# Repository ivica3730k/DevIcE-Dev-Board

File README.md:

# DevIcE-Development-Board
All software materials for DevIcE Development board,created by Ivica 9A3ICE

IoT development board currently is based on ESP8266,including:
SMPS power supply
16 digital IO ports
6 ADC ports
5 DAC outputs
RTC clock
Optional HC-05 bluetooth

...all packed in small form factor of 100*60mm.

Board easly programmable trough Arduino IDE

Full board plans available in other Repo.

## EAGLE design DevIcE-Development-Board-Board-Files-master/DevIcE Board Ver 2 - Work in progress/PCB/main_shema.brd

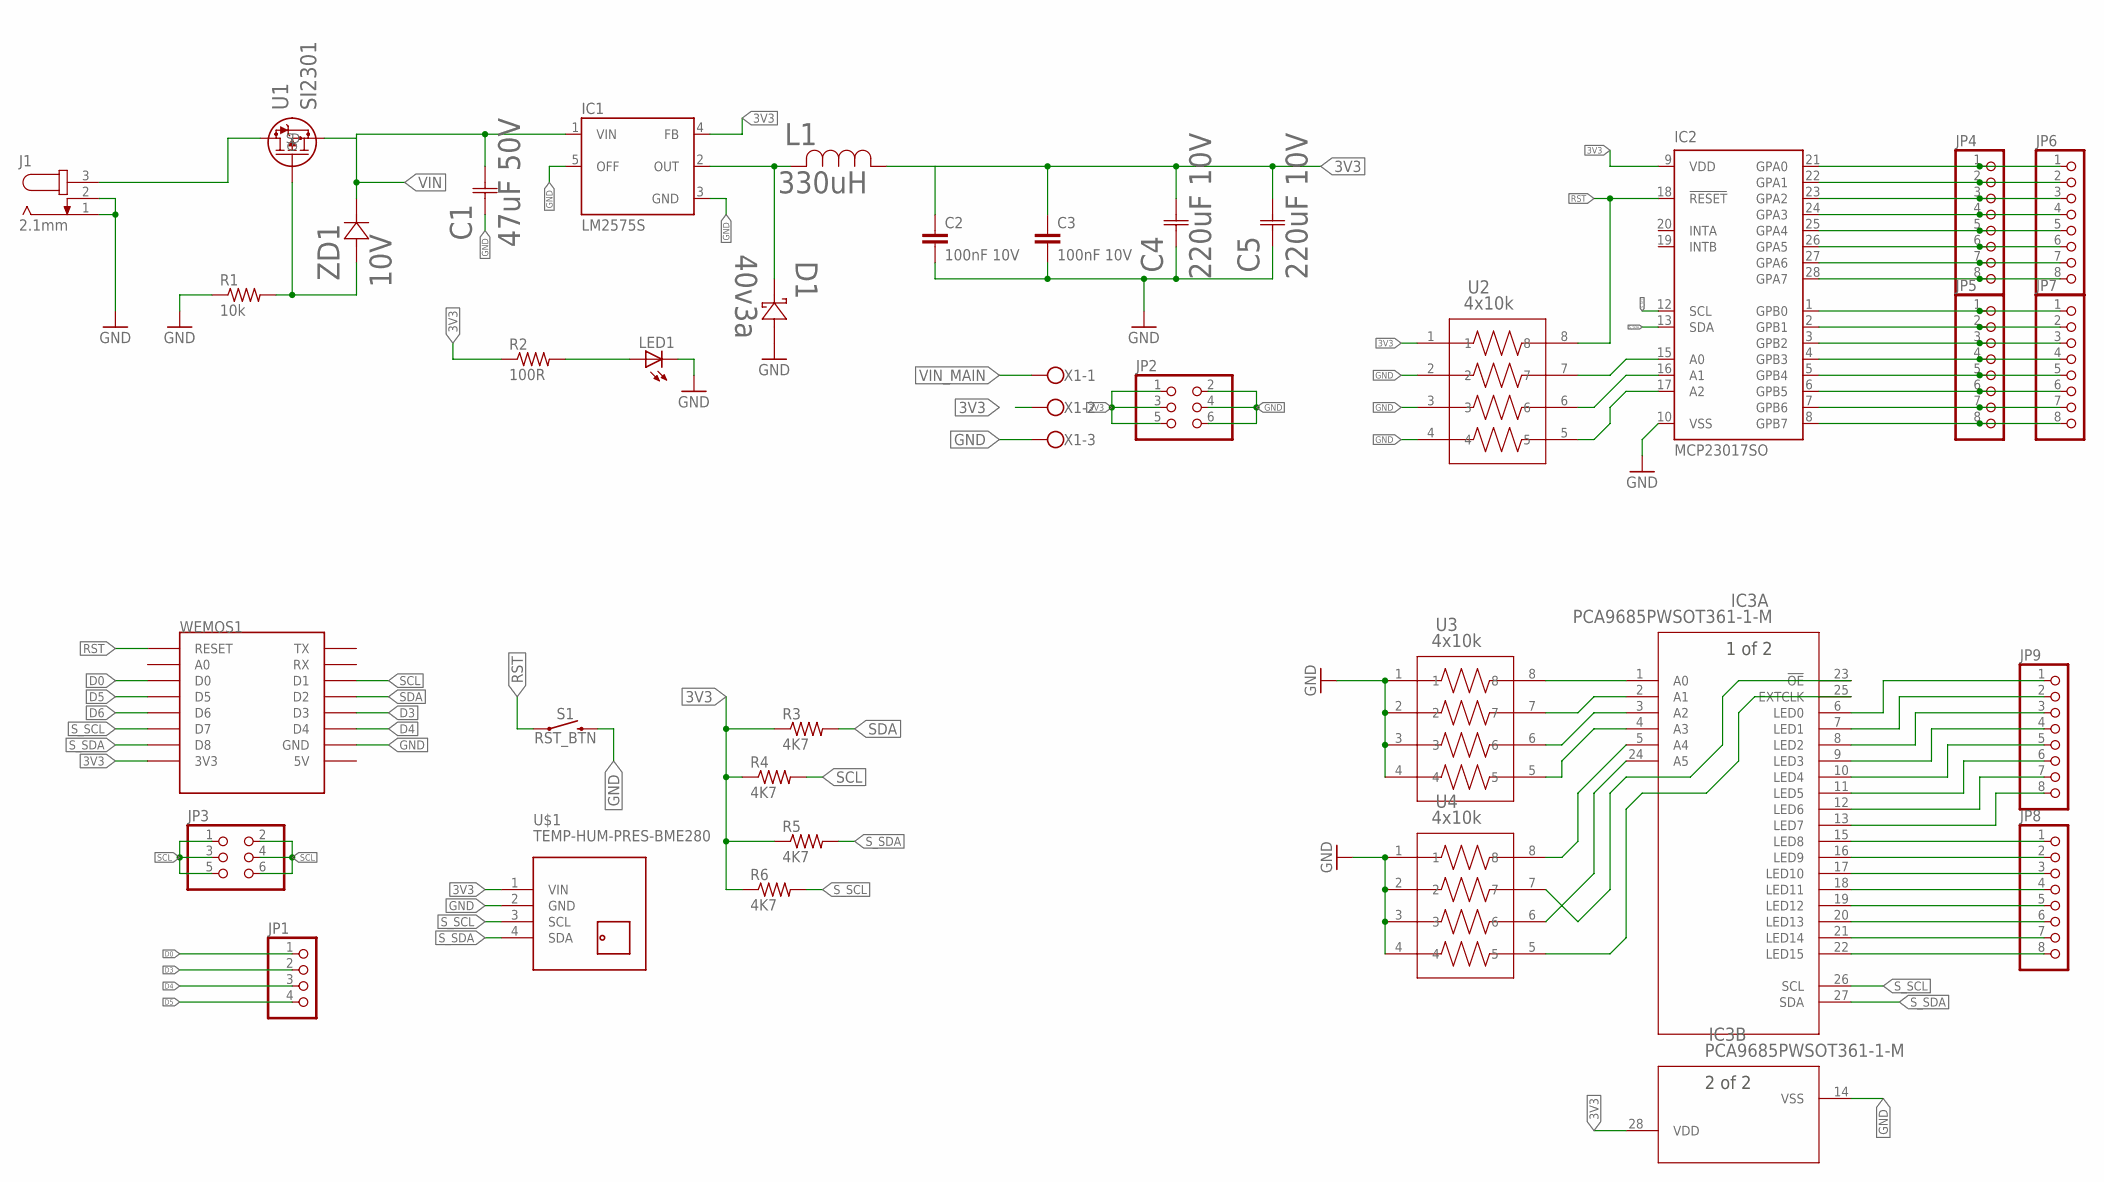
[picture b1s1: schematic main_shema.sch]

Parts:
C1: 47uF 50V; CAP_EEE_D8-M
C2, C3: 100nF 10V; C0603
C4, C5: 220uF 10V; CAP_EEE_D-M
D1: 40v3a; CDBA-HF-M
IC1: LM2575S; TO263-5
IC2: MCP23017SO; SO28W
IC3: PCA9685PWSOT361-1-M; SOT361-1-M
J1: 2.1mm; SPC4078
JP1: PINHD-1X4; 1X04
JP2, JP3: PINHD-2X3; 2X03
JP4, JP5, JP6, JP7: PINHD-1X8; 1X08
JP8, JP9: PINHD-1X8/LONG; 1X08
L1: 330uH; IND_BOURNS_SRR1280
LED1: LED_E; LED_1206
R1: 10k; R0603
R2: 100R; R0603
R3, R4, R5, R6: 4K7; R0603
S1: RST_BTN; TACTILE_SWITCH_PTH_6.0MM
U1: SI2301; TO-236-M
U2: 4x10k; C_ARRAY_EXB38V
U3, U4: 4x10k; C_ARRAY_EXB38V-M
U$1: TEMP-HUM-PRES-BME280
WEMOS1: WEMOS-D1-MINI
X1: W237-103
ZD1: 10V; SMINI2-F5-B-M

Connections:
3V3: C2.1, C3.1, C4.2 (22), C5.2 (22), IC1.4 (FB), IC2.9 (VDD), IC3.28 (VDD), JP2.1, JP2.3, JP2.5, L1.1, R2.1, R3.1, R4.1, R5.1, R6.1, U2.1, U$1.1 (VIN), WEMOS1.3V3, X1.2
D0: JP1.1, WEMOS1.D0
D3: JP1.2, WEMOS1.D3
D4: JP1.3, WEMOS1.D4
D5: JP1.4, WEMOS1.D5
D6: WEMOS1.D6
GND: C1.1 (11), C2.2, C3.2, C4.1 (11), C5.1 (11), D1.2 (22), IC1.3 (GND), IC1.5 (OFF), IC2.10 (VSS), IC3.14 (VSS), J1.1, J1.2, JP2.2, JP2.4, JP2.6, LED1.C, R1.1, S1.3 (2), U2.2, U2.3, U2.4, U3.1, U3.2, U3.3, U3.4, U4.1, U4.2, U4.3, U4.4, U$1.2 (GND), WEMOS1.GND, X1.3
unnamed: LED1.A, R2.2
unnamed: R1.2, U1.1 (G), ZD1.2 (22)
unnamed: IC2.21 (GPA0), JP4.1, JP6.1
unnamed: IC2.22 (GPA1), JP4.2, JP6.2
unnamed: IC3.6 (LED0), JP9.1
unnamed: IC3.7 (LED1), JP9.2
unnamed: IC3.8 (LED2), JP9.3
unnamed: D1.1 (11), IC1.2 (OUT), L1.2
unnamed: IC2.15 (A0), U2.7
unnamed: IC3.9 (LED3), JP9.4
unnamed: IC2.23 (GPA2), JP4.3, JP6.3
unnamed: IC2.16 (A1), U2.6
unnamed: IC2.17 (A2), U2.5
unnamed: IC3.10 (LED4), JP9.5
unnamed: IC2.24 (GPA3), JP4.4, JP6.4
unnamed: IC2.25 (GPA4), JP4.5, JP6.5
unnamed: IC2.26 (GPA5), JP4.6, JP6.6
unnamed: IC3.11 (LED5), JP9.6
unnamed: IC3.12 (LED6), JP9.7
unnamed: IC3.13 (LED7), JP9.8
unnamed: IC2.27 (GPA6), JP4.7, JP6.7
unnamed: IC2.28 (GPA7), JP4.8, JP6.8
unnamed: IC2.1 (GPB0), JP5.1, JP7.1
unnamed: IC2.2 (GPB1), JP5.2, JP7.2
unnamed: IC2.3 (GPB2), JP5.3, JP7.3
unnamed: IC2.4 (GPB3), JP5.4, JP7.4
unnamed: IC2.5 (GPB4), JP5.5, JP7.5
unnamed: IC2.6 (GPB5), JP5.6, JP7.6
unnamed: IC2.7 (GPB6), JP5.7, JP7.7
unnamed: IC2.8 (GPB7), JP5.8, JP7.8
unnamed: IC3.15 (LED8), JP8.1
unnamed: IC3.16 (LED9), JP8.2
unnamed: IC3.17 (LED10), JP8.3
unnamed: IC3.18 (LED11), JP8.4
unnamed: IC3.19 (LED12), JP8.5
unnamed: IC3.20 (LED13), JP8.6
unnamed: IC3.21 (LED14), JP8.7
unnamed: IC3.22 (LED15), JP8.8
unnamed: IC3.1 (A0), U3.8
unnamed: IC3.2 (A1), U3.7
unnamed: IC3.3 (A2), U3.6
unnamed: IC3.4 (A3), U3.5
unnamed: IC3.5 (A4), U4.8
unnamed: IC3.24 (A5), U4.6
unnamed: IC3.23 (!OE), U4.7
unnamed: IC3.25 (EXTCLK), U4.5
RST: IC2.18 (!RESET), S1.1, U2.8, WEMOS1.RESET
SCL: JP3.1, JP3.3, JP3.5, R4.2, WEMOS1.D1
SDA: JP3.2, JP3.4, JP3.6, R3.2, WEMOS1.D2
S_SCL: IC2.12 (SCL), IC3.26 (SCL), R6.2, U$1.3 (SCL), WEMOS1.D7
S_SDA: IC2.13 (SDA), IC3.27 (SDA), R5.2, U$1.4 (SDA), WEMOS1.D8
VIN: C1.2 (22), IC1.1 (VIN), U1.2 (S), ZD1.1 (11)
VIN_MAIN: J1.3, U1.3 (D), X1.1

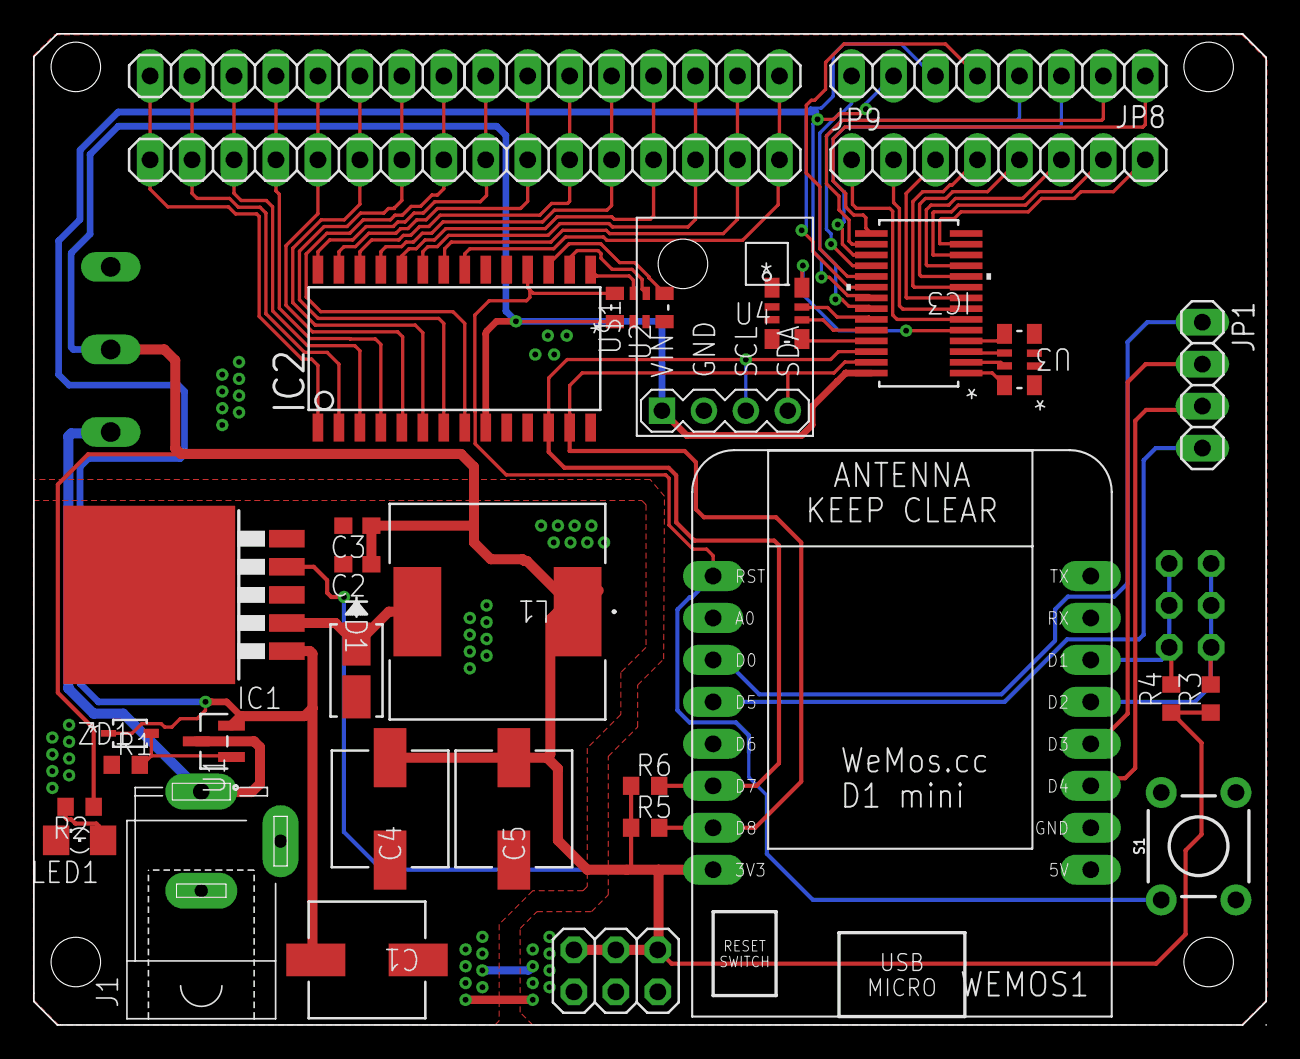
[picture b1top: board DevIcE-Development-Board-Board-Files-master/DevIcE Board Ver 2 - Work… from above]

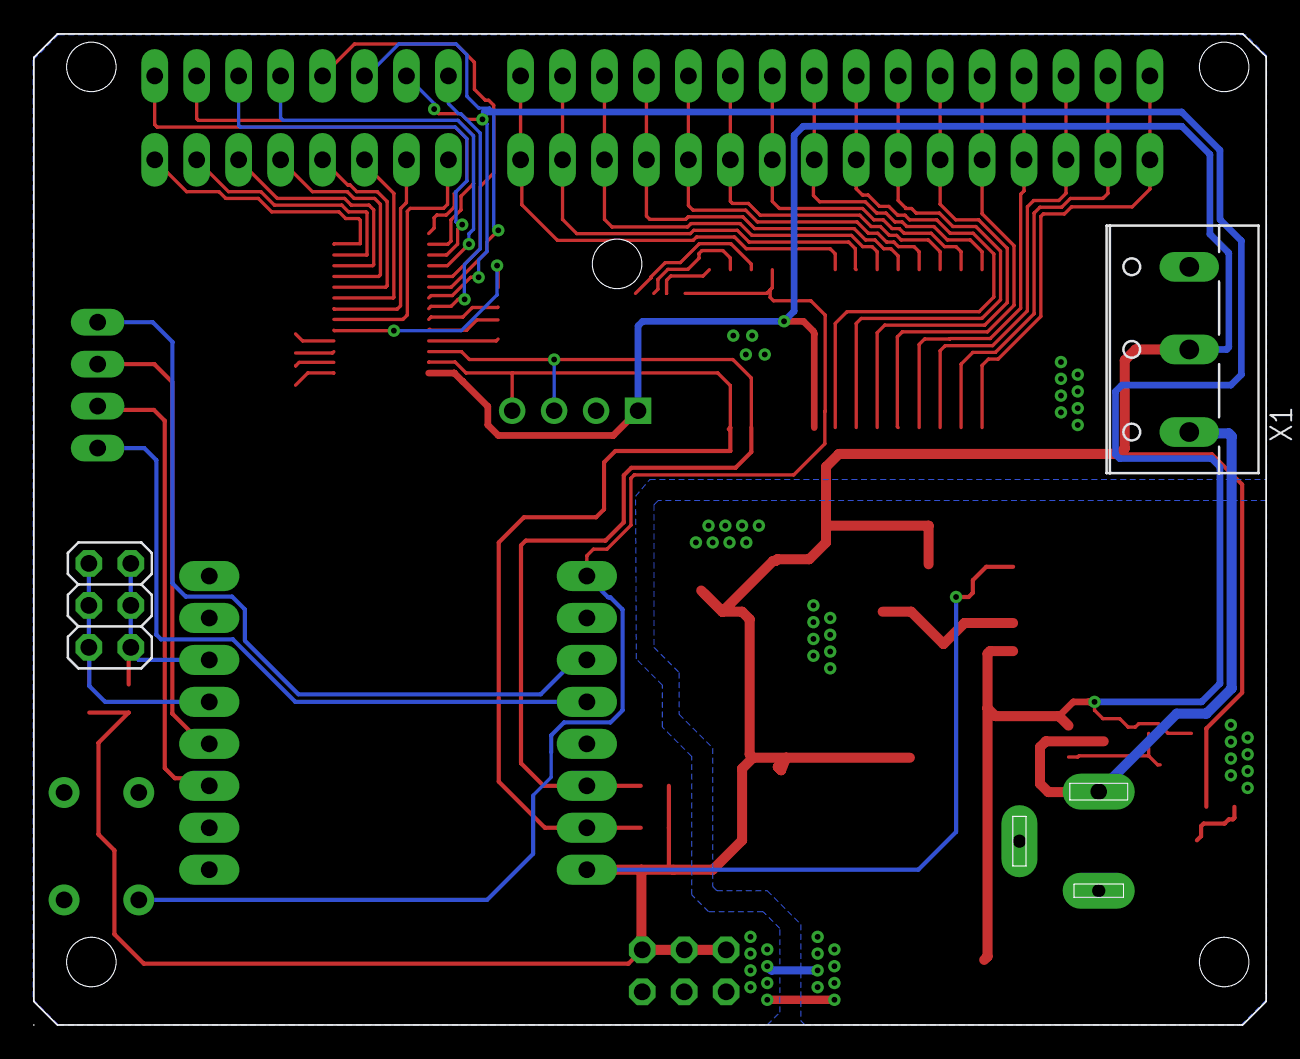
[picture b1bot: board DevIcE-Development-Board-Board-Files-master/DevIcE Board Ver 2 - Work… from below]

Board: 2 copper layers, 74.6 x 60.0 mm, 36 parts (2 on the bottom side), 59 nets.

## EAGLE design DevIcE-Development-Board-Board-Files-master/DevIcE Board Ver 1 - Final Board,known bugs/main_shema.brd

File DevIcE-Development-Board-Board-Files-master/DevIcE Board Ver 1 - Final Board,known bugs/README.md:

DevIcE-Development-Board (Board Files)

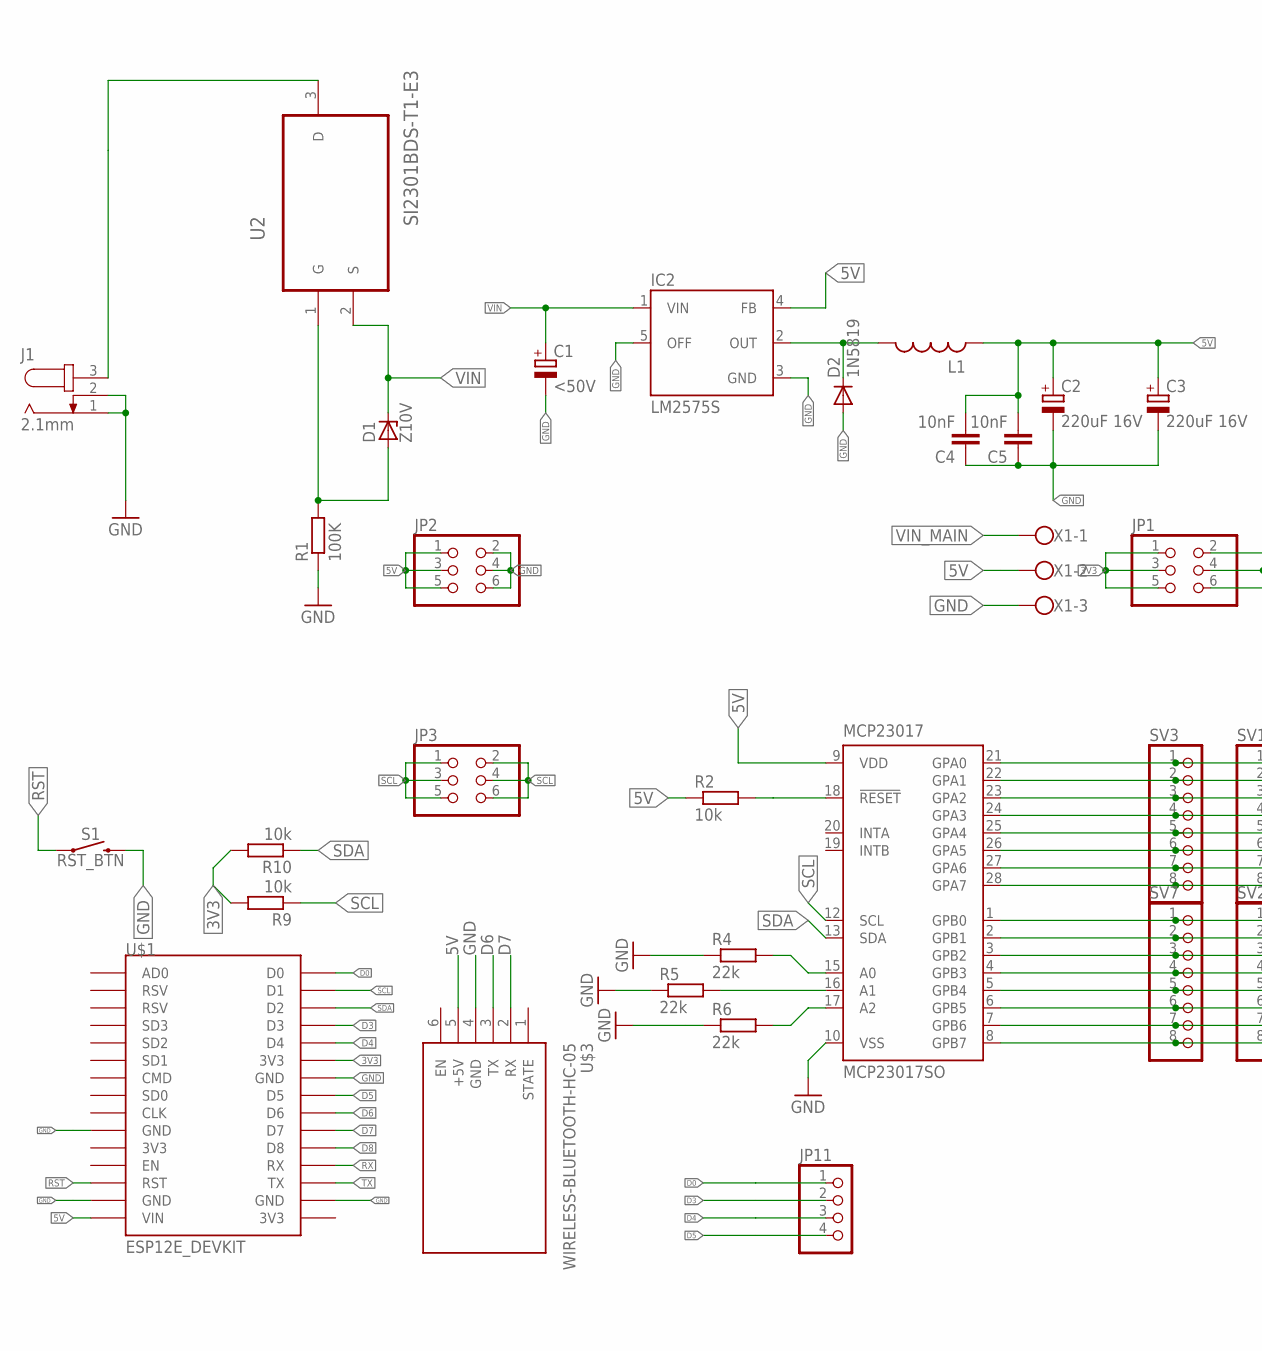
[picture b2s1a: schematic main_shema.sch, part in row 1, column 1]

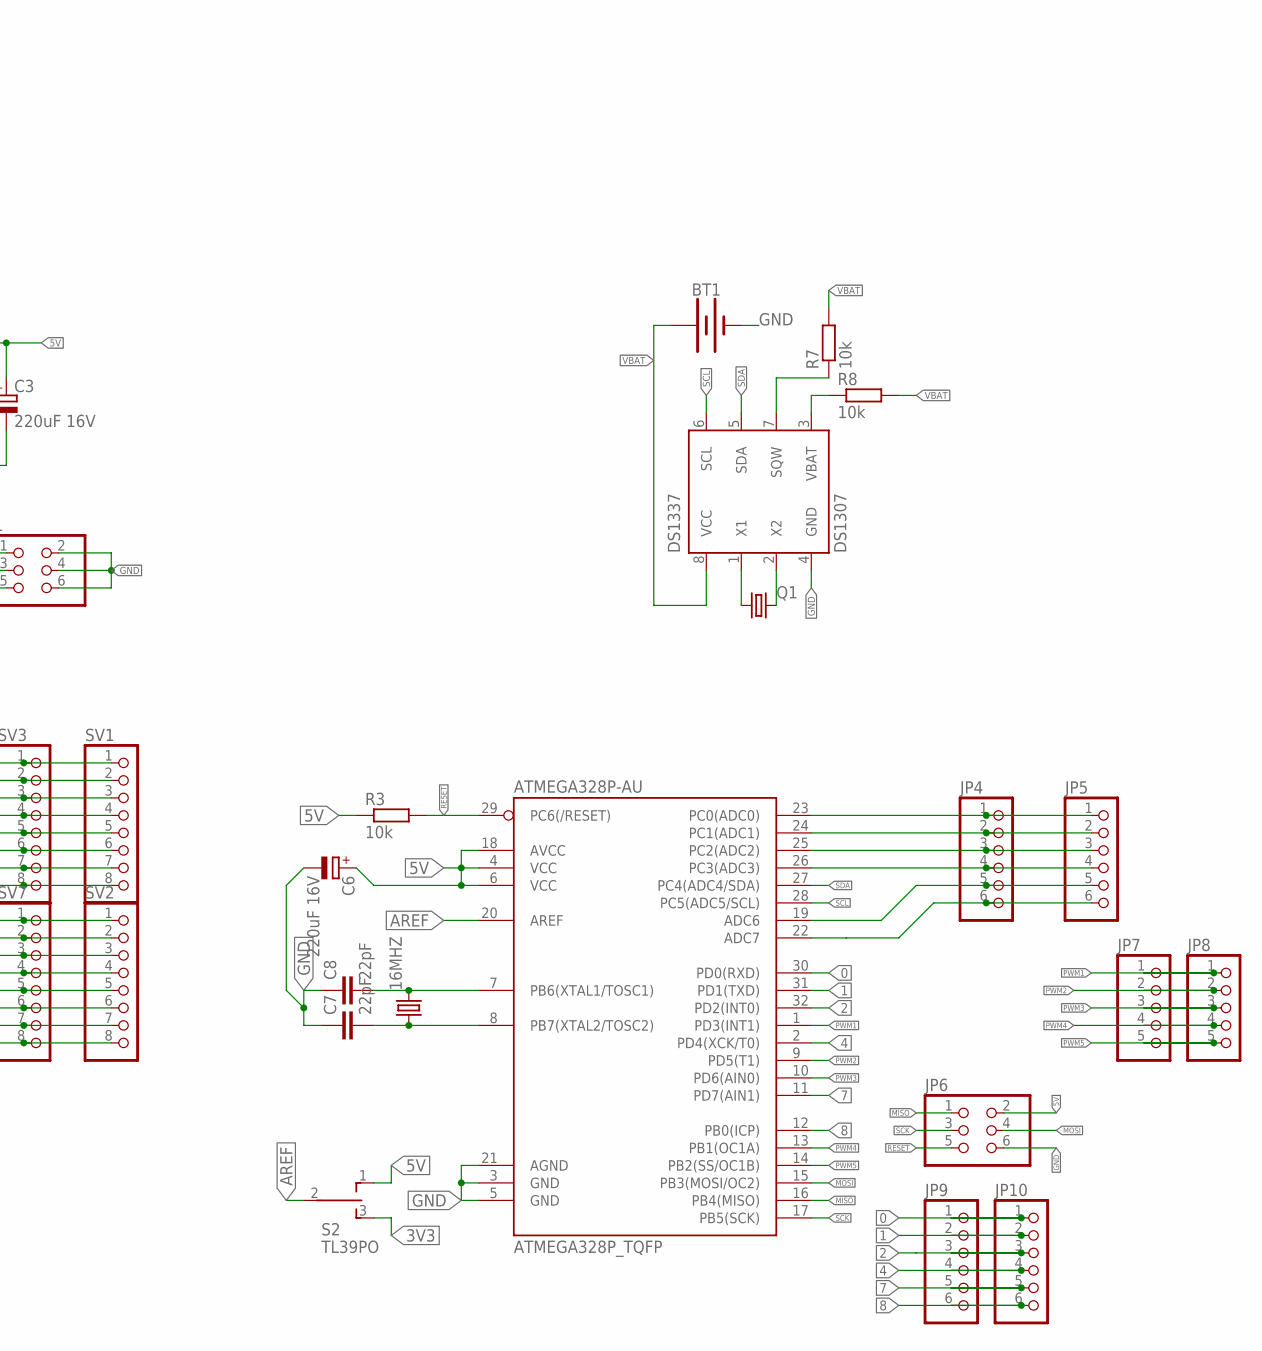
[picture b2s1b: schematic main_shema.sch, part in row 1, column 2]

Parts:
16MHZ: CRYSTALHC49S; HC49/S
ATMEGA328P-AU: ATMEGA328P_TQFP; TQFP32-08
BT1: BATTERY-20MM_PTH; BATTCOM_20MM_PTH
C1: <50V; E3,5-8
C2, C3, C6: 220uF 16V; E2-5
C4, C5: 10nF; C025-024X044
C7, C8: 22pF; C025-024X044
D1: Z10V; DO35Z10
D2: 1N5819; DO41-10
DS1337: DS1307; DIL08
IC2: LM2575S; TO263-5
J1: 2.1mm; SPC4078
JP1, JP2, JP3, JP6: PINHD-2X3; 2X03
JP4, JP5, JP9, JP10: PINHD-1X6; 1X06
JP7, JP8: PINHD-1X5; 1X05
JP11: PINHD-1X4; 1X04
L1: MSS1260
MCP23017: MCP23017SO; SO28W
Q1: CRYSTALTC38H; TC38H
R1: 100K; R1206
R2, R3, R7, R8, R9, R10: 10k; R1206
R4, R5, R6: 22k; R1206
S1: RST_BTN; TACTILE_SWITCH_PTH_6.0MM
S2: TL39PO; TL3XPO
SV1, SV2, SV3, SV7: PINHD-1X8; 1X08
U2: SI2301BDS-T1-E3; SOT95P237X112-3N
U$1: ESP12E_DEVKIT
U$3: WIRELESS-BLUETOOTH-HC-05
X1: W237-103

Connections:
0: ATMEGA328P-AU.30 (PD0(RXD)), JP9.1, JP10.1
1: ATMEGA328P-AU.31 (PD1(TXD)), JP9.2, JP10.2
2: ATMEGA328P-AU.32 (PD2(INT0)), JP9.3, JP10.3
3V3: JP1.1, JP1.3, JP1.5, R9.2, R10.2, S2.3 (S), U$1.3V3@1 (3V3)
4: ATMEGA328P-AU.2 (PD4(XCK/T0)), JP9.4, JP10.4
5V: ATMEGA328P-AU.4 (VCC), ATMEGA328P-AU.6 (VCC), ATMEGA328P-AU.18 (AVCC), C2.+, C3.+, C4.2, C5.2, C6.+, IC2.4 (FB), JP2.1, JP2.3, JP2.5, JP6.2, L1.P$2, MCP23017.9 (VDD), R2.1, R3.1, S2.1 (O), U$1.VIN, U$3.5 (+5V), X1.2
7: ATMEGA328P-AU.11 (PD7(AIN1)), JP9.5, JP10.5
8: ATMEGA328P-AU.12 (PB0(ICP)), JP9.6, JP10.6
AREF: ATMEGA328P-AU.20 (AREF), S2.2
D0: JP11.1, U$1.D0
D3: JP11.2, U$1.D3
D4: JP11.3, U$1.D4
D5: JP11.4, U$1.D5
D6: U$1.D6, U$3.3 (TX)
D7: U$1.D7, U$3.2 (RX)
D8: U$1.D8
GND: ATMEGA328P-AU.3 (GND), ATMEGA328P-AU.5 (GND), ATMEGA328P-AU.21 (AGND), BT1.2 (-), C1.-, C2.-, C3.-, C4.1, C5.1, C6.-, C7.1, C8.1, D2.A, DS1337.4 (GND), IC2.3 (GND), IC2.5 (OFF), J1.1, J1.2, JP1.2, JP1.4, JP1.6, JP2.2, JP2.4, JP2.6, JP6.6, MCP23017.10 (VSS), R1.1, R4.1, R5.1, R6.1, S1.3 (2), U$1.GND@0 (GND), U$1.GND@1 (GND), U$1.GND@2 (GND), U$1.GND@3 (GND), U$3.4 (GND), X1.3
MISO: ATMEGA328P-AU.16 (PB4(MISO)), JP6.1
MOSI: ATMEGA328P-AU.15 (PB3(MOSI/OC2)), JP6.4
unnamed: DS1337.1 (X1), Q1.1
unnamed: D1.A, R1.2, U2.1 (G)
unnamed: MCP23017.21 (GPA0), SV1.1, SV3.1
unnamed: MCP23017.22 (GPA1), SV1.2, SV3.2
unnamed: MCP23017.15 (A0), R4.2
unnamed: MCP23017.16 (A1), R5.2
unnamed: MCP23017.17 (A2), R6.2
unnamed: D2.C, IC2.2 (OUT), L1.P$1
unnamed: DS1337.2 (X2), Q1.2
unnamed: ATMEGA328P-AU.22 (ADC7), JP4.6, JP5.6
unnamed: MCP23017.23 (GPA2), SV1.3, SV3.3
unnamed: DS1337.3 (VBAT), R8.1
unnamed: DS1337.7 (SQW), R7.1
unnamed: MCP23017.24 (GPA3), SV1.4, SV3.4
unnamed: MCP23017.25 (GPA4), SV1.5, SV3.5
unnamed: MCP23017.26 (GPA5), SV1.6, SV3.6
unnamed: MCP23017.18 (!RESET), R2.2
unnamed: 16MHZ.2, ATMEGA328P-AU.7 (PB6(XTAL1/TOSC1)), C8.2
unnamed: 16MHZ.1, ATMEGA328P-AU.8 (PB7(XTAL2/TOSC2)), C7.2
unnamed: MCP23017.27 (GPA6), SV1.7, SV3.7
unnamed: MCP23017.28 (GPA7), SV1.8, SV3.8
unnamed: MCP23017.1 (GPB0), SV2.1, SV7.1
unnamed: MCP23017.2 (GPB1), SV2.2, SV7.2
unnamed: MCP23017.3 (GPB2), SV2.3, SV7.3
unnamed: MCP23017.4 (GPB3), SV2.4, SV7.4
unnamed: MCP23017.5 (GPB4), SV2.5, SV7.5
unnamed: MCP23017.6 (GPB5), SV2.6, SV7.6
unnamed: MCP23017.7 (GPB6), SV2.7, SV7.7
unnamed: MCP23017.8 (GPB7), SV2.8, SV7.8
unnamed: ATMEGA328P-AU.23 (PC0(ADC0)), JP4.1, JP5.1
unnamed: ATMEGA328P-AU.24 (PC1(ADC1)), JP4.2, JP5.2
unnamed: ATMEGA328P-AU.25 (PC2(ADC2)), JP4.3, JP5.3
unnamed: ATMEGA328P-AU.26 (PC3(ADC3)), JP4.4, JP5.4
unnamed: ATMEGA328P-AU.19 (ADC6), JP4.5, JP5.5
PWM1: ATMEGA328P-AU.1 (PD3(INT1)), JP7.1, JP8.1
PWM2: ATMEGA328P-AU.9 (PD5(T1)), JP7.2, JP8.2
PWM3: ATMEGA328P-AU.10 (PD6(AIN0)), JP7.3, JP8.3
PWM4: ATMEGA328P-AU.13 (PB1(OC1A)), JP7.4, JP8.4
PWM5: ATMEGA328P-AU.14 (PB2(SS/OC1B)), JP7.5, JP8.5
RESET: ATMEGA328P-AU.29 (PC6(/RESET)), JP6.5, R3.2
RST: S1.1, U$1.RST
RX: U$1.RX
SCK: ATMEGA328P-AU.17 (PB5(SCK)), JP6.3
SCL: ATMEGA328P-AU.28 (PC5(ADC5/SCL)), DS1337.6 (SCL), JP3.1, JP3.3, JP3.5, MCP23017.12 (SCL), R9.1, U$1.D1
SDA: ATMEGA328P-AU.27 (PC4(ADC4/SDA)), DS1337.5 (SDA), JP3.2, JP3.4, JP3.6, MCP23017.13 (SDA), R10.1, U$1.D2
TX: U$1.TX
VBAT: BT1.1 (+), DS1337.8 (VCC), R7.2, R8.2
VIN: C1.+, D1.C, IC2.1 (VIN), U2.2 (S)
VIN_MAIN: J1.3, U2.3 (D), X1.1

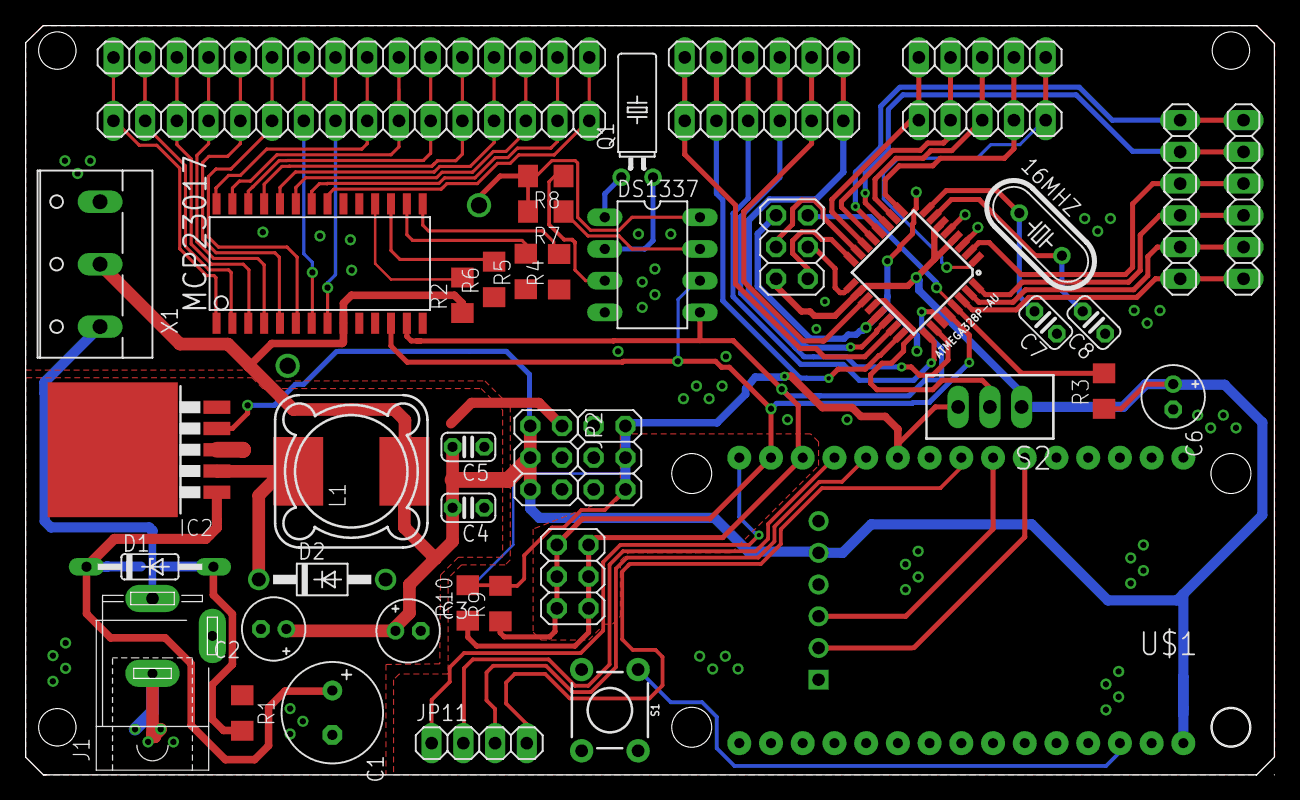
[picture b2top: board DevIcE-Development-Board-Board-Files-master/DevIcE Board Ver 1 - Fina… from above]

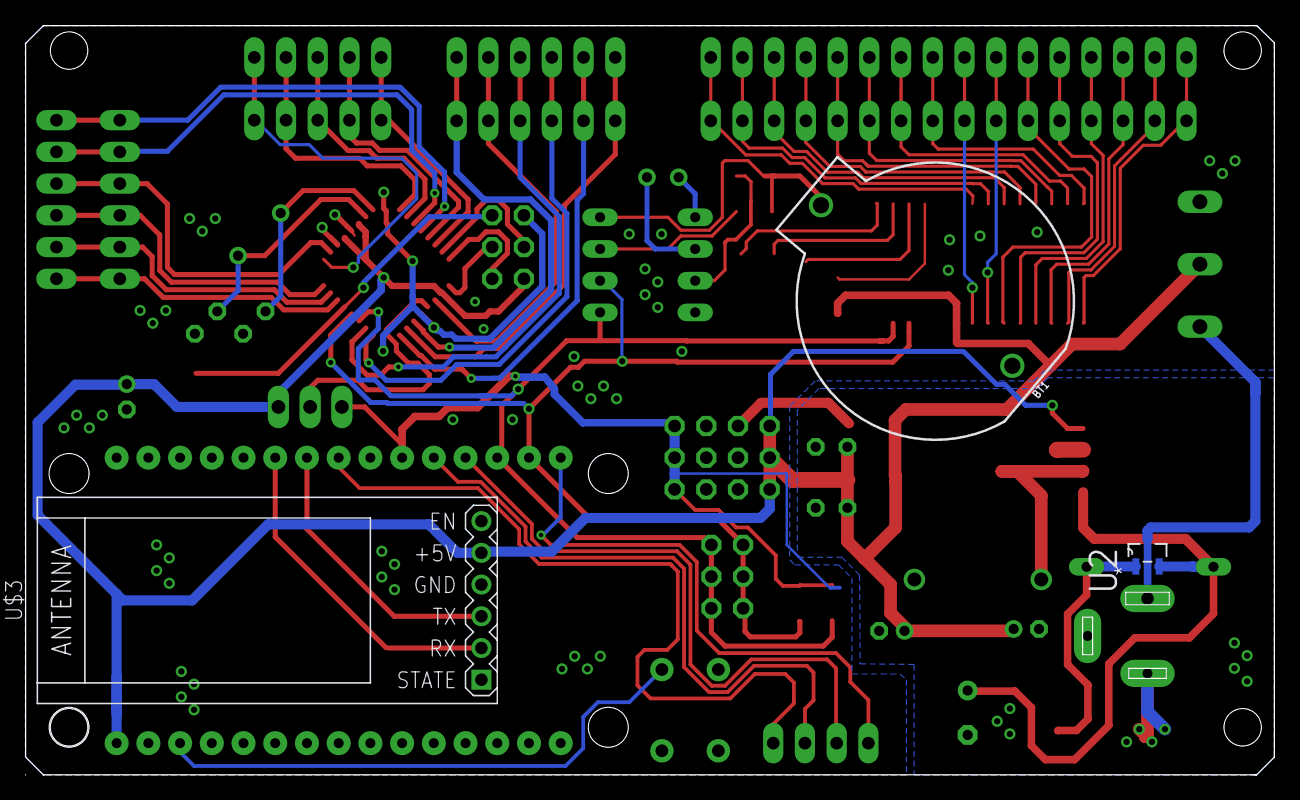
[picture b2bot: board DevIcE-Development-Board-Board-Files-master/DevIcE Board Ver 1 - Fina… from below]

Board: 2 copper layers, 100.0 x 60.0 mm, 50 parts (3 on the bottom side), 65 nets.

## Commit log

2018-06-04 First library update for DevIcE Development Board
    Library is writen in C++
    Adafruit's library for MCP23017 is used to make thing easier.
2018-06-18 Library update and added example
2018-07-11 Fix on .gitignore
2018-08-25 Fixing library mess
2019-11-18 Merged all versions from other repos

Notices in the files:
parts and their libraries:
diy-modules: Released under the Creative Commons Attribution 4.0 International License: http://creativecommons.org/licenses/by/4.0
SparkFun-Batteries: Licensing: Creative Commons ShareAlike 4.0 International - https://creativecommons.org/licenses/by-sa/4.0
